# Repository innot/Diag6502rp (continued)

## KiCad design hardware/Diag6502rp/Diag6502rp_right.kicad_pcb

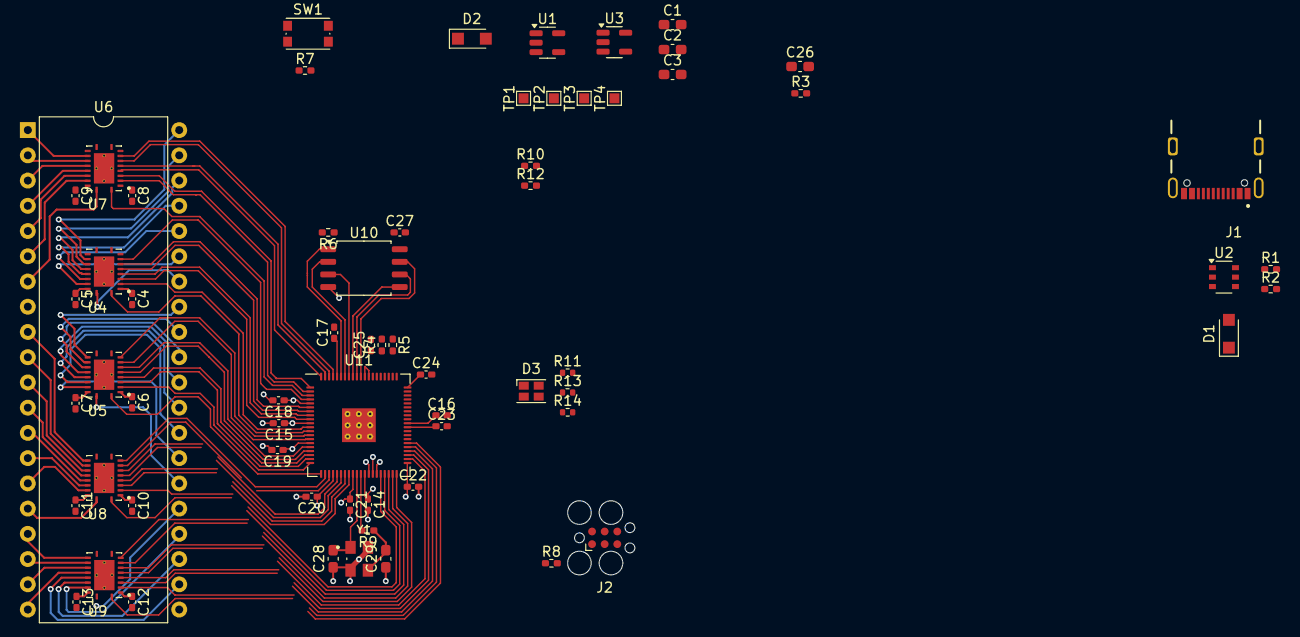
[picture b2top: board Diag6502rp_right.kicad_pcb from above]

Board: 4 copper layers, 65 parts (0 on the bottom side), 111 nets.

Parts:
C1, C3, C26: 2.2u; C_0603_1608Metric_Pad1.08x0.95mm_HandSolder
C2: 10u; C_0603_1608Metric_Pad1.08x0.95mm_HandSolder
C4, C5, C6, C7, C8, C9, C10, C11, C12, C13, C15, C16, C17, C18, C19, C20, C21, C22, C23, C24, C25, C27: 0.1u; C_0402_1005Metric_Pad0.74x0.62mm_HandSolder
C14: 4.7u; C_0402_1005Metric_Pad0.74x0.62mm_HandSolder
C28, C29: 15p; C_0603_1608Metric_Pad1.08x0.95mm_HandSolder
D1, D2: PMEG3010ER; Nexperia_CFP3_SOD-123W
D3: LED_ABGR; LED_Cree-PLCC4_2x2mm_CW
J1: USB4105-G-FA; GCT_USB4105-GF-A
J2: Conn_ARM_SWD_TagConnect_TC2030; Tag-Connect_TC2030-IDC-FP_2x03_P1.27mm_Vertical
R1, R2, R10, R12: 5.1k; R_0402_1005Metric_Pad0.72x0.64mm_HandSolder
R3: 10; R_0402_1005Metric_Pad0.72x0.64mm_HandSolder
R4, R5: 27; R_0402_1005Metric_Pad0.72x0.64mm_HandSolder
R6: 10k; R_0402_1005Metric_Pad0.72x0.64mm_HandSolder
R7, R8, R9: 1k; R_0402_1005Metric_Pad0.72x0.64mm_HandSolder
R11, R13, R14: 680; R_0402_1005Metric
SW1: SW_Push; SW_Push_1P1T_NO_CK_KMR2
TP1: +1V1; TestPoint_Pad_1.0x1.0mm
TP2: V_{BUS}; TestPoint_Pad_1.0x1.0mm
TP3: V_{SUP}; TestPoint_Pad_1.0x1.0mm
TP4: +3V3; TestPoint_Pad_1.0x1.0mm
U1: TLV74311P; SOT-23-5
U2: IP4234CZ6; TSOP-6_1.65x3.05mm_P0.95mm
U3: AP2112K-3.3; SOT-23-5
U4, U5, U7, U8, U9: TXS0108EPW; IC_TXS0108ERGYR
U6: 65x02x_Universal; DIP-40_W15.24mm
U10: W25Q128JVS; SOIC-8_5.23x5.23mm_P1.27mm
U11: RP2350_80QFN; RP2350-QFN-80-1EP_10x10_P0.4mm_EP3.4x3.4mm_ThermalVias
Y1: ABM8-272-T3; XTAL_ABM8-272-T3

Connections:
+1V1: C1.1, C14.1, C15.1, C16.1, TP1.1, U1.5 (OUT), U11.10 (DVDD), U11.32 (DVDD), U11.51 (DVDD)
+3V3: C3.1, C4.1, C6.1, C8.1, C10.1, C12.1, C17.1, C18.1, C19.1, C20.1, C21.1, C22.1, C23.1, C24.1, C25.1, C27.1, D3.1 (A), J2.1 (VCC), R3.1, R6.1, R8.2, TP4.1, U3.5 (VOUT), U4.2 (VCCA), U4.10 (OE), U5.2 (VCCA), U5.10 (OE), U7.2 (VCCA), U7.10 (OE), U8.2 (VCCA), U8.10 (OE), U9.2 (VCCA), U9.10 (OE), U10.8 (VCC), U11.5 (IOVDD), U11.15 (IOVDD), U11.24 (IOVDD), U11.29 (IOVDD), U11.41 (IOVDD), U11.50 (IOVDD), U11.59 (ADC_AVDD), U11.60 (IOVDD), U11.68 (USB_OTP_VDD), U11.69 (QSPI_IOVDD), U11.76 (IOVDD)
+5V: C5.1, C7.1, C9.1, C11.1, C13.1, D2.2 (A), R10.2, U4.19 (VCCB), U5.19 (VCCB), U6.8 (Vcc), U7.19 (VCCB), U8.19 (VCCB), U9.19 (VCCB)
/Level Shifters & CPU Interface/6502_A0: U6.9 (A0), U8.12 (B8)
/Level Shifters & CPU Interface/6502_A1: U6.10 (A1), U8.13 (B7)
/Level Shifters & CPU Interface/6502_A2: U6.11 (A2), U8.14 (B6)
/Level Shifters & CPU Interface/6502_A3: U6.12 (A3), U8.15 (B5)
/Level Shifters & CPU Interface/6502_A4: U6.13 (A4), U8.16 (B4)
/Level Shifters & CPU Interface/6502_A5: U6.14 (A5), U8.17 (B3)
/Level Shifters & CPU Interface/6502_A6: U6.15 (A6), U8.18 (B2)
/Level Shifters & CPU Interface/6502_A7: U6.16 (A7), U8.20 (B1)
/Level Shifters & CPU Interface/6502_A8: U6.17 (A8), U9.12 (B8)
/Level Shifters & CPU Interface/6502_A9: U6.18 (A9), U9.13 (B7)
/Level Shifters & CPU Interface/6502_A10: U6.19 (A10), U9.14 (B6)
/Level Shifters & CPU Interface/6502_A11: U6.20 (A11), U9.15 (B5)
/Level Shifters & CPU Interface/6502_A12: U6.22 (A12), U9.16 (B4)
/Level Shifters & CPU Interface/6502_A13: U6.23 (A13), U9.17 (B3)
/Level Shifters & CPU Interface/6502_A14: U6.24 (A14), U9.18 (B2)
/Level Shifters & CPU Interface/6502_A15: U6.25 (A15), U9.20 (B1)
/Level Shifters & CPU Interface/6502_D0: U5.12 (B8), U6.33 (D0)
/Level Shifters & CPU Interface/6502_D1: U5.13 (B7), U6.32 (D1)
/Level Shifters & CPU Interface/6502_D2: U5.14 (B6), U6.31 (D2)
/Level Shifters & CPU Interface/6502_D3: U5.15 (B5), U6.30 (D3)
/Level Shifters & CPU Interface/6502_D4: U5.16 (B4), U6.29 (D4)
/Level Shifters & CPU Interface/6502_D5: U5.17 (B3), U6.28 (D5)
/Level Shifters & CPU Interface/6502_D6: U5.18 (B2), U6.27 (D6)
/Level Shifters & CPU Interface/6502_D7: U5.20 (B1), U6.26 (D7)
/Level Shifters & CPU Interface/6502_PHI0: U4.16 (B4), U6.37 (ϕ0)
/Level Shifters & CPU Interface/6502_PHI1: U6.3 (ϕ1), U7.15 (B5)
/Level Shifters & CPU Interface/6502_PHI2: U4.14 (B6), U6.39 (ϕ2)
/Level Shifters & CPU Interface/6502_PIN1: U6.1 (Vss/~VP/Vss), U7.13 (B7)
/Level Shifters & CPU Interface/6502_PIN5: U6.5 (NC/~ML/NC), U7.17 (B3)
/Level Shifters & CPU Interface/6502_PIN35: U4.18 (B2), U6.35 (NC/NC/~HALT)
/Level Shifters & CPU Interface/6502_PIN36: U4.17 (B3), U6.36 (NC/BE/R/~W)
/Level Shifters & CPU Interface/6502_RDY: U6.2 (RDY), U7.14 (B6)
/Level Shifters & CPU Interface/6502_R/~W: U4.20 (B1), U6.34 (R/~W)
/Level Shifters & CPU Interface/6502_SYNC: U6.7 (SYNC), U7.20 (B1)
/Level Shifters & CPU Interface/6502_~IRQ: U6.4 (~IRQ), U7.16 (B4)
/Level Shifters & CPU Interface/6502_~NMI: U6.6 (~NMI), U7.18 (B2)
/Level Shifters & CPU Interface/6502_~RES: U4.13 (B7), U6.40 (~RES)
/Level Shifters & CPU Interface/6502_~SO: U4.15 (B5), U6.38 (~SO)
/Level Shifters & CPU Interface/A0: U8.9 (A8), U11.22 (GPIO22)
/Level Shifters & CPU Interface/A1: U8.8 (A7), U11.23 (GPIO23)
/Level Shifters & CPU Interface/A2: U8.7 (A6), U11.25 (GPIO24)
/Level Shifters & CPU Interface/A3: U8.6 (A5), U11.26 (GPIO25)
/Level Shifters & CPU Interface/A4: U8.5 (A4), U11.27 (GPIO26)
/Level Shifters & CPU Interface/A5: U8.4 (A3), U11.28 (GPIO27)
/Level Shifters & CPU Interface/A6: U8.3 (A2), U11.36 (GPIO28)
/Level Shifters & CPU Interface/A7: U8.1 (A1), U11.37 (GPIO29)
/Level Shifters & CPU Interface/A8: U9.9 (A8), U11.38 (GPIO30)
/Level Shifters & CPU Interface/A9: U9.8 (A7), U11.39 (GPIO31)
/Level Shifters & CPU Interface/A10: U9.7 (A6), U11.40 (GPIO32)
/Level Shifters & CPU Interface/A11: U9.6 (A5), U11.42 (GPIO33)
/Level Shifters & CPU Interface/A12: U9.5 (A4), U11.43 (GPIO34)
/Level Shifters & CPU Interface/A13: U9.4 (A3), U11.44 (GPIO35)
/Level Shifters & CPU Interface/A14: U9.3 (A2), U11.45 (GPIO36)
/Level Shifters & CPU Interface/A15: U9.1 (A1), U11.46 (GPIO37)
/Level Shifters & CPU Interface/CTRL.PHI0: U4.5 (A4), U11.8 (GPIO10)
/Level Shifters & CPU Interface/CTRL.PHI1: U7.6 (A5), U11.79 (GPIO2)
/Level Shifters & CPU Interface/CTRL.PHI2: U4.7 (A6), U11.6 (GPIO8)
/Level Shifters & CPU Interface/CTRL.PIN1: U7.8 (A7), U11.77 (GPIO0)
/Level Shifters & CPU Interface/CTRL.PIN5: U7.4 (A3), U11.1 (GPIO4)
/Level Shifters & CPU Interface/CTRL.PIN35: U4.3 (A2), U11.11 (GPIO12)
/Level Shifters & CPU Interface/CTRL.PIN36: U4.4 (A3), U11.9 (GPIO11)
/Level Shifters & CPU Interface/CTRL.RDY: U7.7 (A6), U11.78 (GPIO1)
/Level Shifters & CPU Interface/CTRL.RW: U4.1 (A1), U11.12 (GPIO13)
/Level Shifters & CPU Interface/CTRL.SYNC: U7.1 (A1), U11.3 (GPIO6)
/Level Shifters & CPU Interface/CTRL.~IRQ: U7.5 (A4), U11.80 (GPIO3)
/Level Shifters & CPU Interface/CTRL.~NMI: U7.3 (A2), U11.2 (GPIO5)
/Level Shifters & CPU Interface/CTRL.~RES: U4.8 (A7), U11.4 (GPIO7)
/Level Shifters & CPU Interface/CTRL.~SO: U4.6 (A5), U11.7 (GPIO9)
/Level Shifters & CPU Interface/D0: U5.9 (A8), U11.13 (GPIO14)
/Level Shifters & CPU Interface/D1: U5.8 (A7), U11.14 (GPIO15)
/Level Shifters & CPU Interface/D2: U5.7 (A6), U11.16 (GPIO16)
/Level Shifters & CPU Interface/D3: U5.6 (A5), U11.17 (GPIO17)
/Level Shifters & CPU Interface/D4: U5.5 (A4), U11.18 (GPIO18)
/Level Shifters & CPU Interface/D5: U5.4 (A3), U11.19 (GPIO19)
/Level Shifters & CPU Interface/D6: U5.3 (A2), U11.20 (GPIO20)
/Level Shifters & CPU Interface/D7: U5.1 (A1), U11.21 (GPIO21)
/Power Supply & USB/USB_DM: R5.1, U2.3 (I/O1B)
/Power Supply & USB/USB_DP: R4.2, U2.4 (I/O2B)
/Power Supply & USB/V_{SUP}: C2.1, D1.1 (K), D2.1 (K), TP3.1, U1.1 (IN), U1.3 (EN), U3.1 (VIN), U3.3 (EN)
/Processor/5V_SENSE: R10.1, R12.1, U11.49 (GPIO40_ADC0)
/Processor/QSPI_SCLK: U10.6 (CLK), U11.71 (QSPI_SCLK)
/Processor/QSPI_SD0: U10.5 (DI(IO0)), U11.72 (QSPI_SD0)
/Processor/QSPI_SD1: U10.2 (DO(IO1)), U11.74 (QSPI_SD1)
/Processor/QSPI_SD2: U10.3 (IO2), U11.73 (QSPI_SD2)
/Processor/QSPI_SD3: U10.7 (IO3), U11.70 (QSPI_SD3)
/Processor/QSPI_SS: R6.2, R7.2, U10.1 (~CS), U11.75 (QSPI_SS)
/Processor/XIN: C28.2, U11.30 (XIN), Y1.1
/Processor/XOUT: R9.2, U11.31 (XOUT)
/Processor/~RGB_B: R14.1, U11.58 (GPIO47_ADC7)
/Processor/~RGB_G: R13.1, U11.57 (GPIO46_ADC6)
/Processor/~RGB_R: R11.1, U11.56 (GPIO45_ADC5)
GND: C1.2, C2.2, C3.2, C4.2, C5.2, C6.2, C7.2, C8.2, C9.2, C10.2, C11.2, C12.2, C13.2, C14.2, C15.2, C16.2, C17.2, C18.2, C19.2, C20.2, C21.2, C22.2, C23.2, C24.2, C25.2, C26.2, C27.2, C28.1, C29.1, J1.A1_B12 (GND), J1.B1_A12 (GND), J1.SH1 (SHIELD), J1.SH2 (SHIELD), J1.SH3 (SHIELD), J1.SH4 (SHIELD), J2.5 (GND), R1.2, R2.2, R12.2, SW1.1, U1.2 (GND), U2.2 (GND), U3.2 (GND), U4.11 (GND), U4.21 (EP), U4.22 (EP_VIA), U4.23 (EP_VIA), U4.24 (EP_VIA), U4.25 (EP_VIA), U5.11 (GND), U5.21 (EP), U5.22 (EP_VIA), U5.23 (EP_VIA), U5.24 (EP_VIA), U5.25 (EP_VIA), U6.21 (Vss), U7.11 (GND), U7.21 (EP), U7.22 (EP_VIA), U7.23 (EP_VIA), U7.24 (EP_VIA), U7.25 (EP_VIA), U8.11 (GND), U8.21 (EP), U8.22 (EP_VIA), U8.23 (EP_VIA), U8.24 (EP_VIA), U8.25 (EP_VIA), U9.11 (GND), U9.21 (EP), U9.22 (EP_VIA), U9.23 (EP_VIA), U9.24 (EP_VIA), U9.25 (EP_VIA), U10.4 (GND), U11.81 (GND), Y1.2 (GND), Y1.4 (GND)
unnamed: C29.2, R9.1, Y1.3
unnamed: D3.2 (BK), R14.2
unnamed: D3.3 (GK), R13.2
unnamed: D3.4 (RK), R11.2
unnamed: J1.A5 (CC1), R1.1
unnamed: J1.B5 (CC2), R2.1
unnamed: J2.4 (SWCLK), U11.33 (SWCLK)
unnamed: J2.2 (SWDIO), U11.34 (SWD)
unnamed: J2.3 (~RESET), R8.1, U11.35 (RUN)
unnamed: R7.1, SW1.2
unnamed: J1.A7 (D-), J1.B7 (D-), U2.1 (I/O1A)
unnamed: J1.A6 (D+), J1.B6 (D+), U2.6 (I/O2A)
unnamed: R5.2, U11.66 (USB_DM)
unnamed: R4.1, U11.67 (USB_DP)
unnamed: C26.1, R3.2, U11.61 (VREG_AVDD), U11.64 (VREG_VIN)
VBUS: D1.2 (A), J1.A4_B9 (VBUS), J1.B4_A9 (VBUS), TP2.1, U2.5 (VB)

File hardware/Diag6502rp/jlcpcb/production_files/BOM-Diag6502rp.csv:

Comment,Designator,Footprint,LCSC,Quantity
1k,"R7,R8,R9",R_0402_1005Metric,C11702,3
27,"R4,R5",R_0402_1005Metric,C138021,2
0.1u,"C10,C11,C12,C13,C17,C18,C19,C20,C21,C22,C23,C24,C25,C26,C27,C29,C4,C5,C6,C7,C8,C9",C_0402_1005Metric,C1525,22
15p,"C30,C31",C_0402_1005Metric,C1548,2
TXS0108EPWR,"U4,U5,U6,U7,U8",TSSOP-20_4.4x6.5mm_P0.65mm,C17206,5
10u,"C14,C15,C2",C_0603_1608Metric,C19702,3
ABM8-272-T3,Y1,XTAL_ABM8-272-T3,C20625731,1
4.7u,"C1,C16,C28,C3",C_0402_1005Metric,C23733,4
10,R3,R_0402_1005Metric,C25077,1
330,"R11,R13,R14",R_0402_1005Metric,C25104,3
10k,"R15,R6",R_0402_1005Metric,C25744,2
5.1k,"R1,R10,R12,R2",R_0402_1005Metric,C25905,4
GT-USB-7010ASV,J5,USB_C_Receptacle_G-Switch_GT-USB-7010ASV,C2988369,1
RP2350_80QFN,U10,RP2350-QFN-80-1EP_10x10_P0.4mm_EP3.4x3.4mm_ThermalVias,C42415655,1
IP4234CZ6,U2,SC-74-6_1.55x2.9mm_P0.95mm,C455086,1
PMEG3010ER,"D1,D2",Nexperia_CFP3_SOD-123W,C456106,2
TLV74311PDBVR,U1,SOT-23-5,C485147,1
Conn_01x02_PinHeader,J9,PinHeader_1x02_P2.54mm_Vertical,C492401,1
Conn_01x20_PinHeader,"J1,J10,J11,J3",PinHeader_1x20_P2.54mm_Vertical,C50981,4
AP2112K-3.3,U3,SOT-23-5,C51118,1
XZMDKCBDDG45S-9,D3,LED_XZMDKCBDDG45S-9,C5355400,1
TS-1088-AR02016,SW1,TS-1088-xxxxxxx,C720477,1
Conn_01x02_PinSocket,J8,PinSocket_1x02_P2.54mm_Vertical,C7499322,1
Conn_01x20_PinSocket,"J2,J4",PinSocket_1x20_P2.54mm_Vertical,C7499336,2
W25Q128JVS,U9,SOIC-8_5.3x5.3mm_P1.27mm,C97521,1

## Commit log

2025-07-06 Changed TSX0108e foorprint to TSSOP20 for easier routing.
2025-07-06 Main design completed
2025-07-07 Cleanup, Fiduciaries, component spacing
2025-07-07 preparing for assembly
2025-07-12 Added transfer and stitching vias.
2025-07-14 More via separation and transfer vias
2025-07-18 Rev.A
